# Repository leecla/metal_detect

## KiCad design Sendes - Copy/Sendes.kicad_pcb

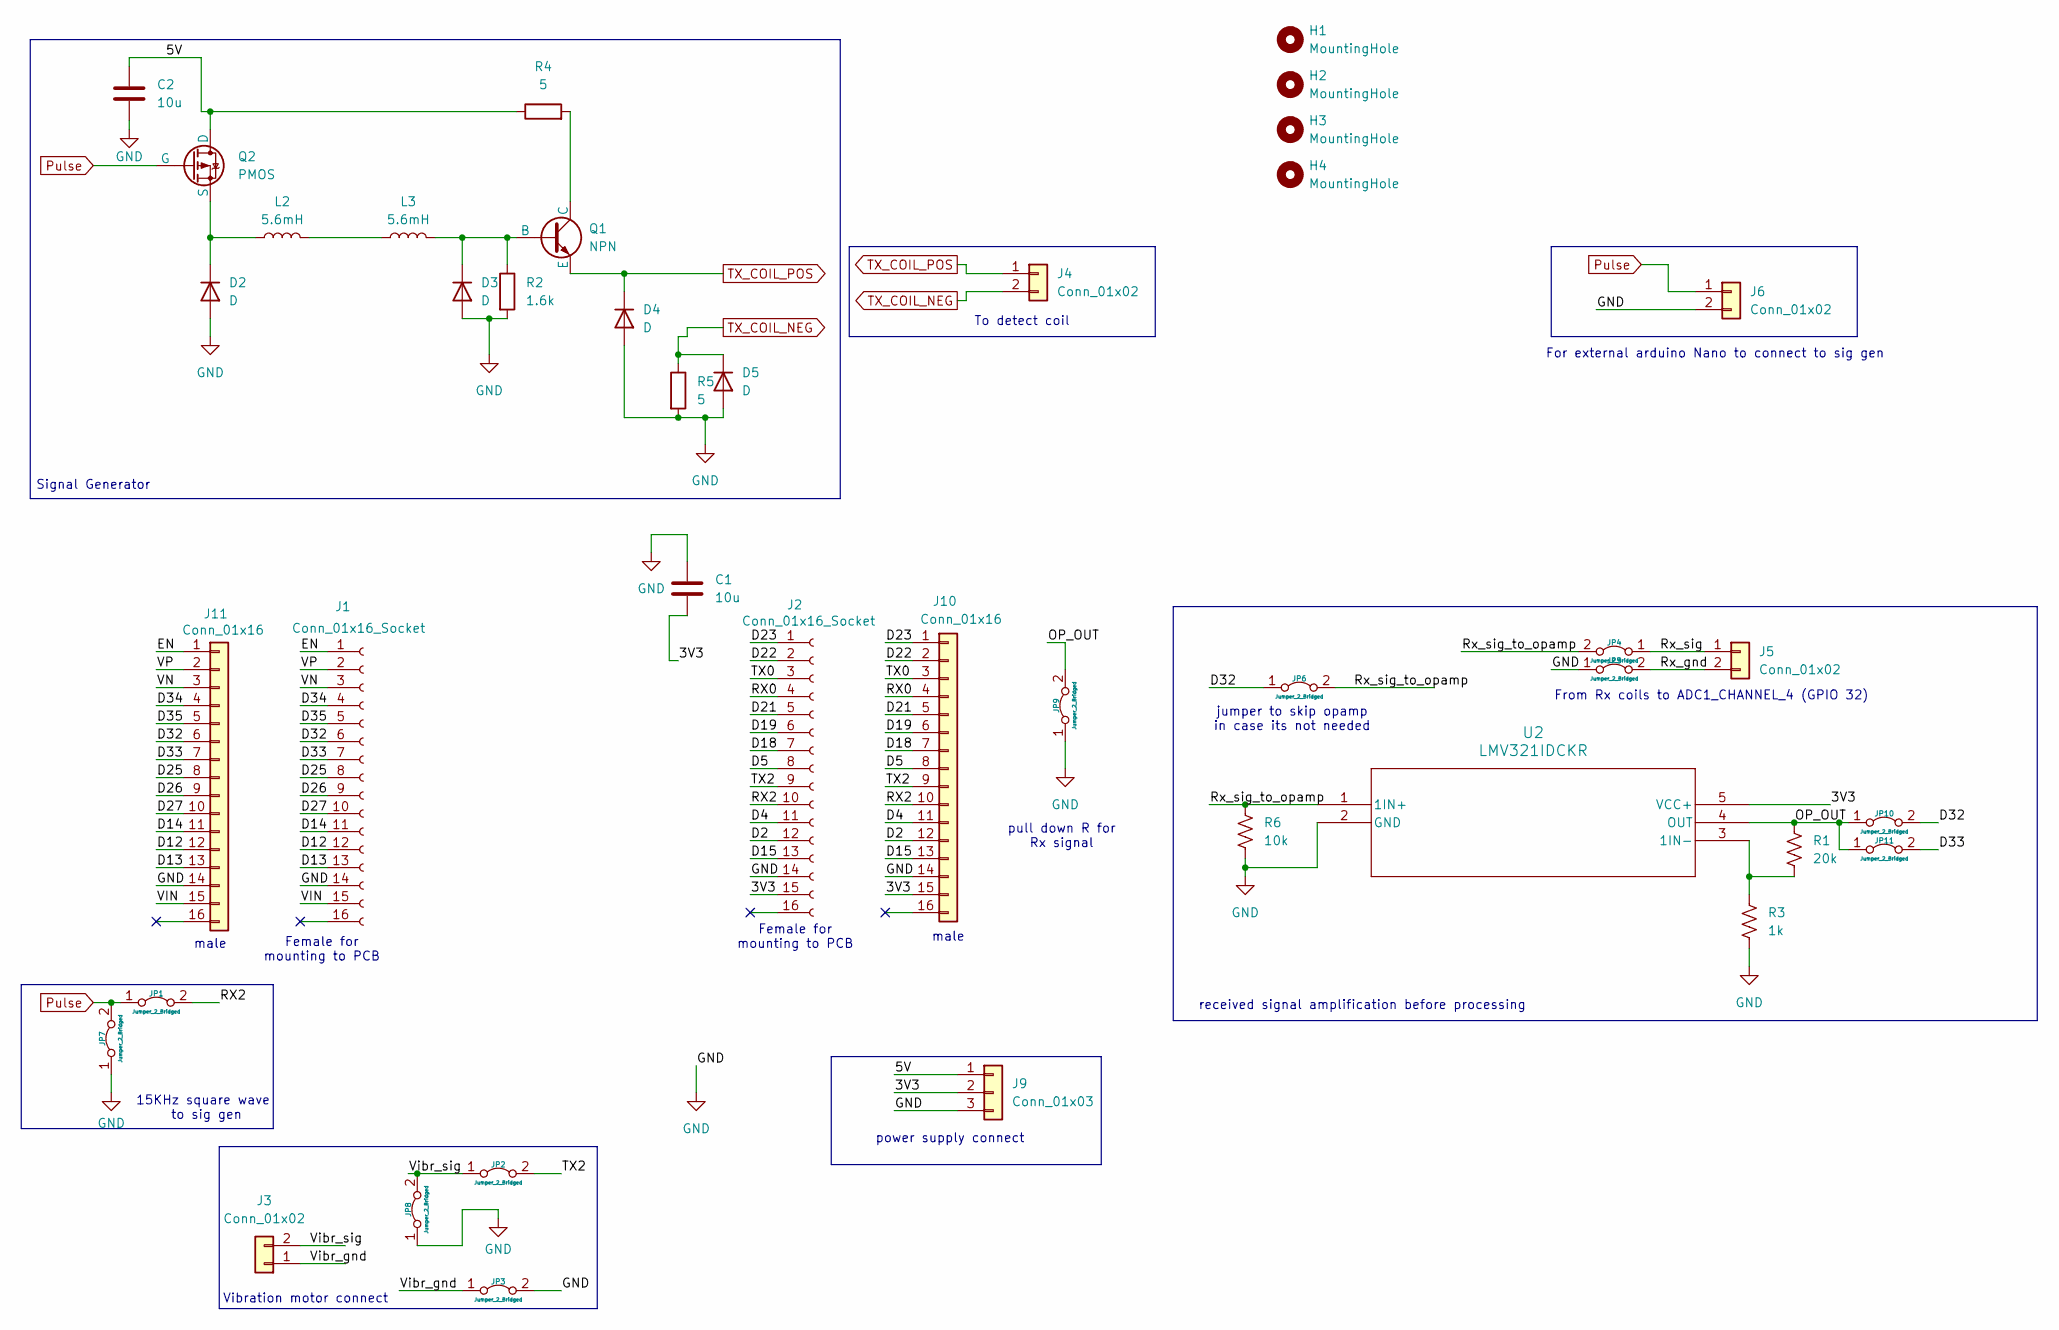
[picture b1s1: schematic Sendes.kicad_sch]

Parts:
C1, C2: 10u; C_0805_2012Metric_Pad1.18x1.45mm_HandSolder
D2, D3, D4, D5: D; D_1206_3216Metric
H1, H2, H3, H4: MountingHole; MountingHole_2.2mm_M2
J1, J2: Conn_01x16_Socket; PinHeader_1x16_P2.54mm_Vertical
J3, J4, J5, J6: Conn_01x02; PinHeader_1x02_P2.54mm_Vertical
J9: Conn_01x03; PinHeader_1x03_P2.54mm_Vertical
J10, J11: Conn_01x16; PinHeader_1x16_P2.54mm_Vertical
JP1, JP2, JP3, JP4, JP5, JP6, JP7, JP8, JP9, JP10, JP11: Jumper_2_Bridged; R_0603_1608Metric_Pad0.98x0.95mm_HandSolder
L2, L3: 5.6mH; L_Radial_D7.8mm_P5.00mm_Fastron_07HCP
Q1: NPN; SOT-23
Q2: PMOS; SOT-23
R1: 20k; R_0603_1608Metric_Pad0.98x0.95mm_HandSolder
R2: 1.6k; R_2512_6332Metric
R3: 1k; R_0603_1608Metric_Pad0.98x0.95mm_HandSolder
R4, R5: 5; R_2512_6332Metric
R6: 10k; R_0603_1608Metric_Pad0.98x0.95mm_HandSolder
U2: LMV321IDCKR; DCK5

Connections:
/3V3: C1.2, J2.15, J9.2, J10.15, U2.5 (VCC+)
/5V: C2.1, J9.1, Q2.1 (D), R4.1
/D2: J2.12, J10.12
/D4: J2.11, J10.11
/D5: J2.8, J10.8
/D12: J1.12, J11.12
/D13: J1.13, J11.13
/D14: J1.11, J11.11
/D15: J2.13, J10.13
/D18: J2.7, J10.7
/D19: J2.6, J10.6
/D21: J2.5, J10.5
/D22: J2.2, J10.2
/D23: J2.1, J10.1
/D25: J1.8, J11.8
/D26: J1.9, J11.9
/D27: J1.10, J11.10
/D32: J1.6, J11.6, JP6.1 (A), JP10.2 (B)
/D33: J1.7, J11.7, JP11.2 (B)
/D34: J1.4, J11.4
/D35: J1.5, J11.5
/EN: J1.1, J11.1
/OP_OUT: JP9.2 (B), JP10.1 (A), JP11.1 (A), R1.1, U2.4 (OUT)
/RX0: J2.4, J10.4
/RX2: J2.10, J10.10, JP1.2 (B)
/Rx_gnd: J5.2, JP5.2 (B)
/Rx_sig: J5.1, JP4.1 (A)
/Rx_sig_to_opamp: JP4.2 (B), JP6.2 (B), R6.1, U2.1 (1IN+)
/TX0: J2.3, J10.3
/TX2: J2.9, J10.9, JP2.2 (B)
/VIN: J1.15, J11.15
/VN: J1.3, J11.3
/VP: J1.2, J11.2
/Vibr_gnd: J3.1, JP3.1 (A)
/Vibr_sig: J3.2, JP2.1 (A), JP8.2 (B)
GND: C1.1, C2.2, D2.2 (A), D3.2 (A), D4.2 (A), D5.2 (A), J1.14, J2.14, J6.2, J9.3, J10.14, J11.14, JP3.2 (B), JP5.1 (A), JP7.1 (A), JP8.1 (A), JP9.1 (A), R2.2, R3.2, R5.2, R6.2, U2.2 (GND)
unnamed: D2.1 (K), L2.1, Q2.3 (S)
unnamed: D3.1 (K), L3.2, Q1.2 (B), R2.1
unnamed: L2.2, L3.1
unnamed: Q1.1 (C), R4.2
unnamed: R1.2, R3.1, U2.3 (1IN-)
Pulse: J6.1, JP1.1 (A), JP7.2 (B), Q2.2 (G)
TX_COIL_NEG: D5.1 (K), J4.2, R5.1
TX_COIL_POS: D4.1 (K), J4.1, Q1.3 (E)

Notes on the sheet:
Female for mounting to PCB
male
To detect coil
pull down R for Rx signal
For external arduino Nano to connect to sig gen
From Rx coils to ADC1_CHANNEL_4 (GPIO 32)
received signal amplification before processing
Signal Generator
jumper to skip opamp in case its not needed
power supply connect
15KHz square wave to sig gen
Vibration motor connect

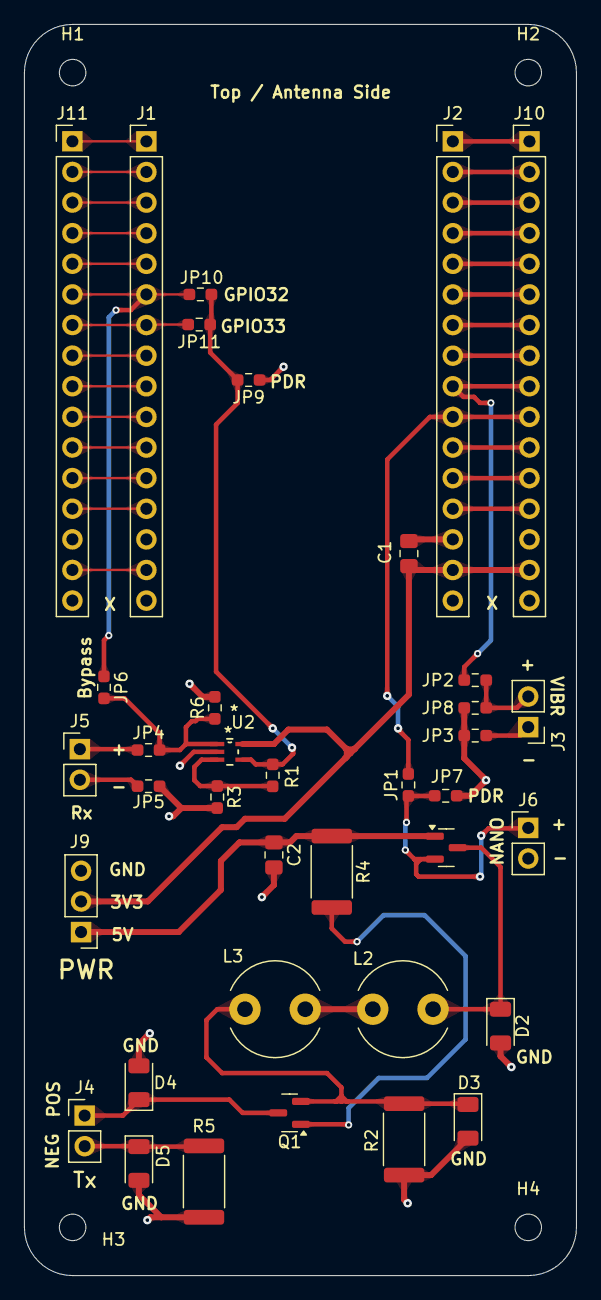
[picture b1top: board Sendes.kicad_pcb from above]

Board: 2 copper layers, 45.8 x 103.8 mm, 41 parts (0 on the bottom side), 44 nets.

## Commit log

2024-04-27 Add files via upload
    Kicad files for PCB
